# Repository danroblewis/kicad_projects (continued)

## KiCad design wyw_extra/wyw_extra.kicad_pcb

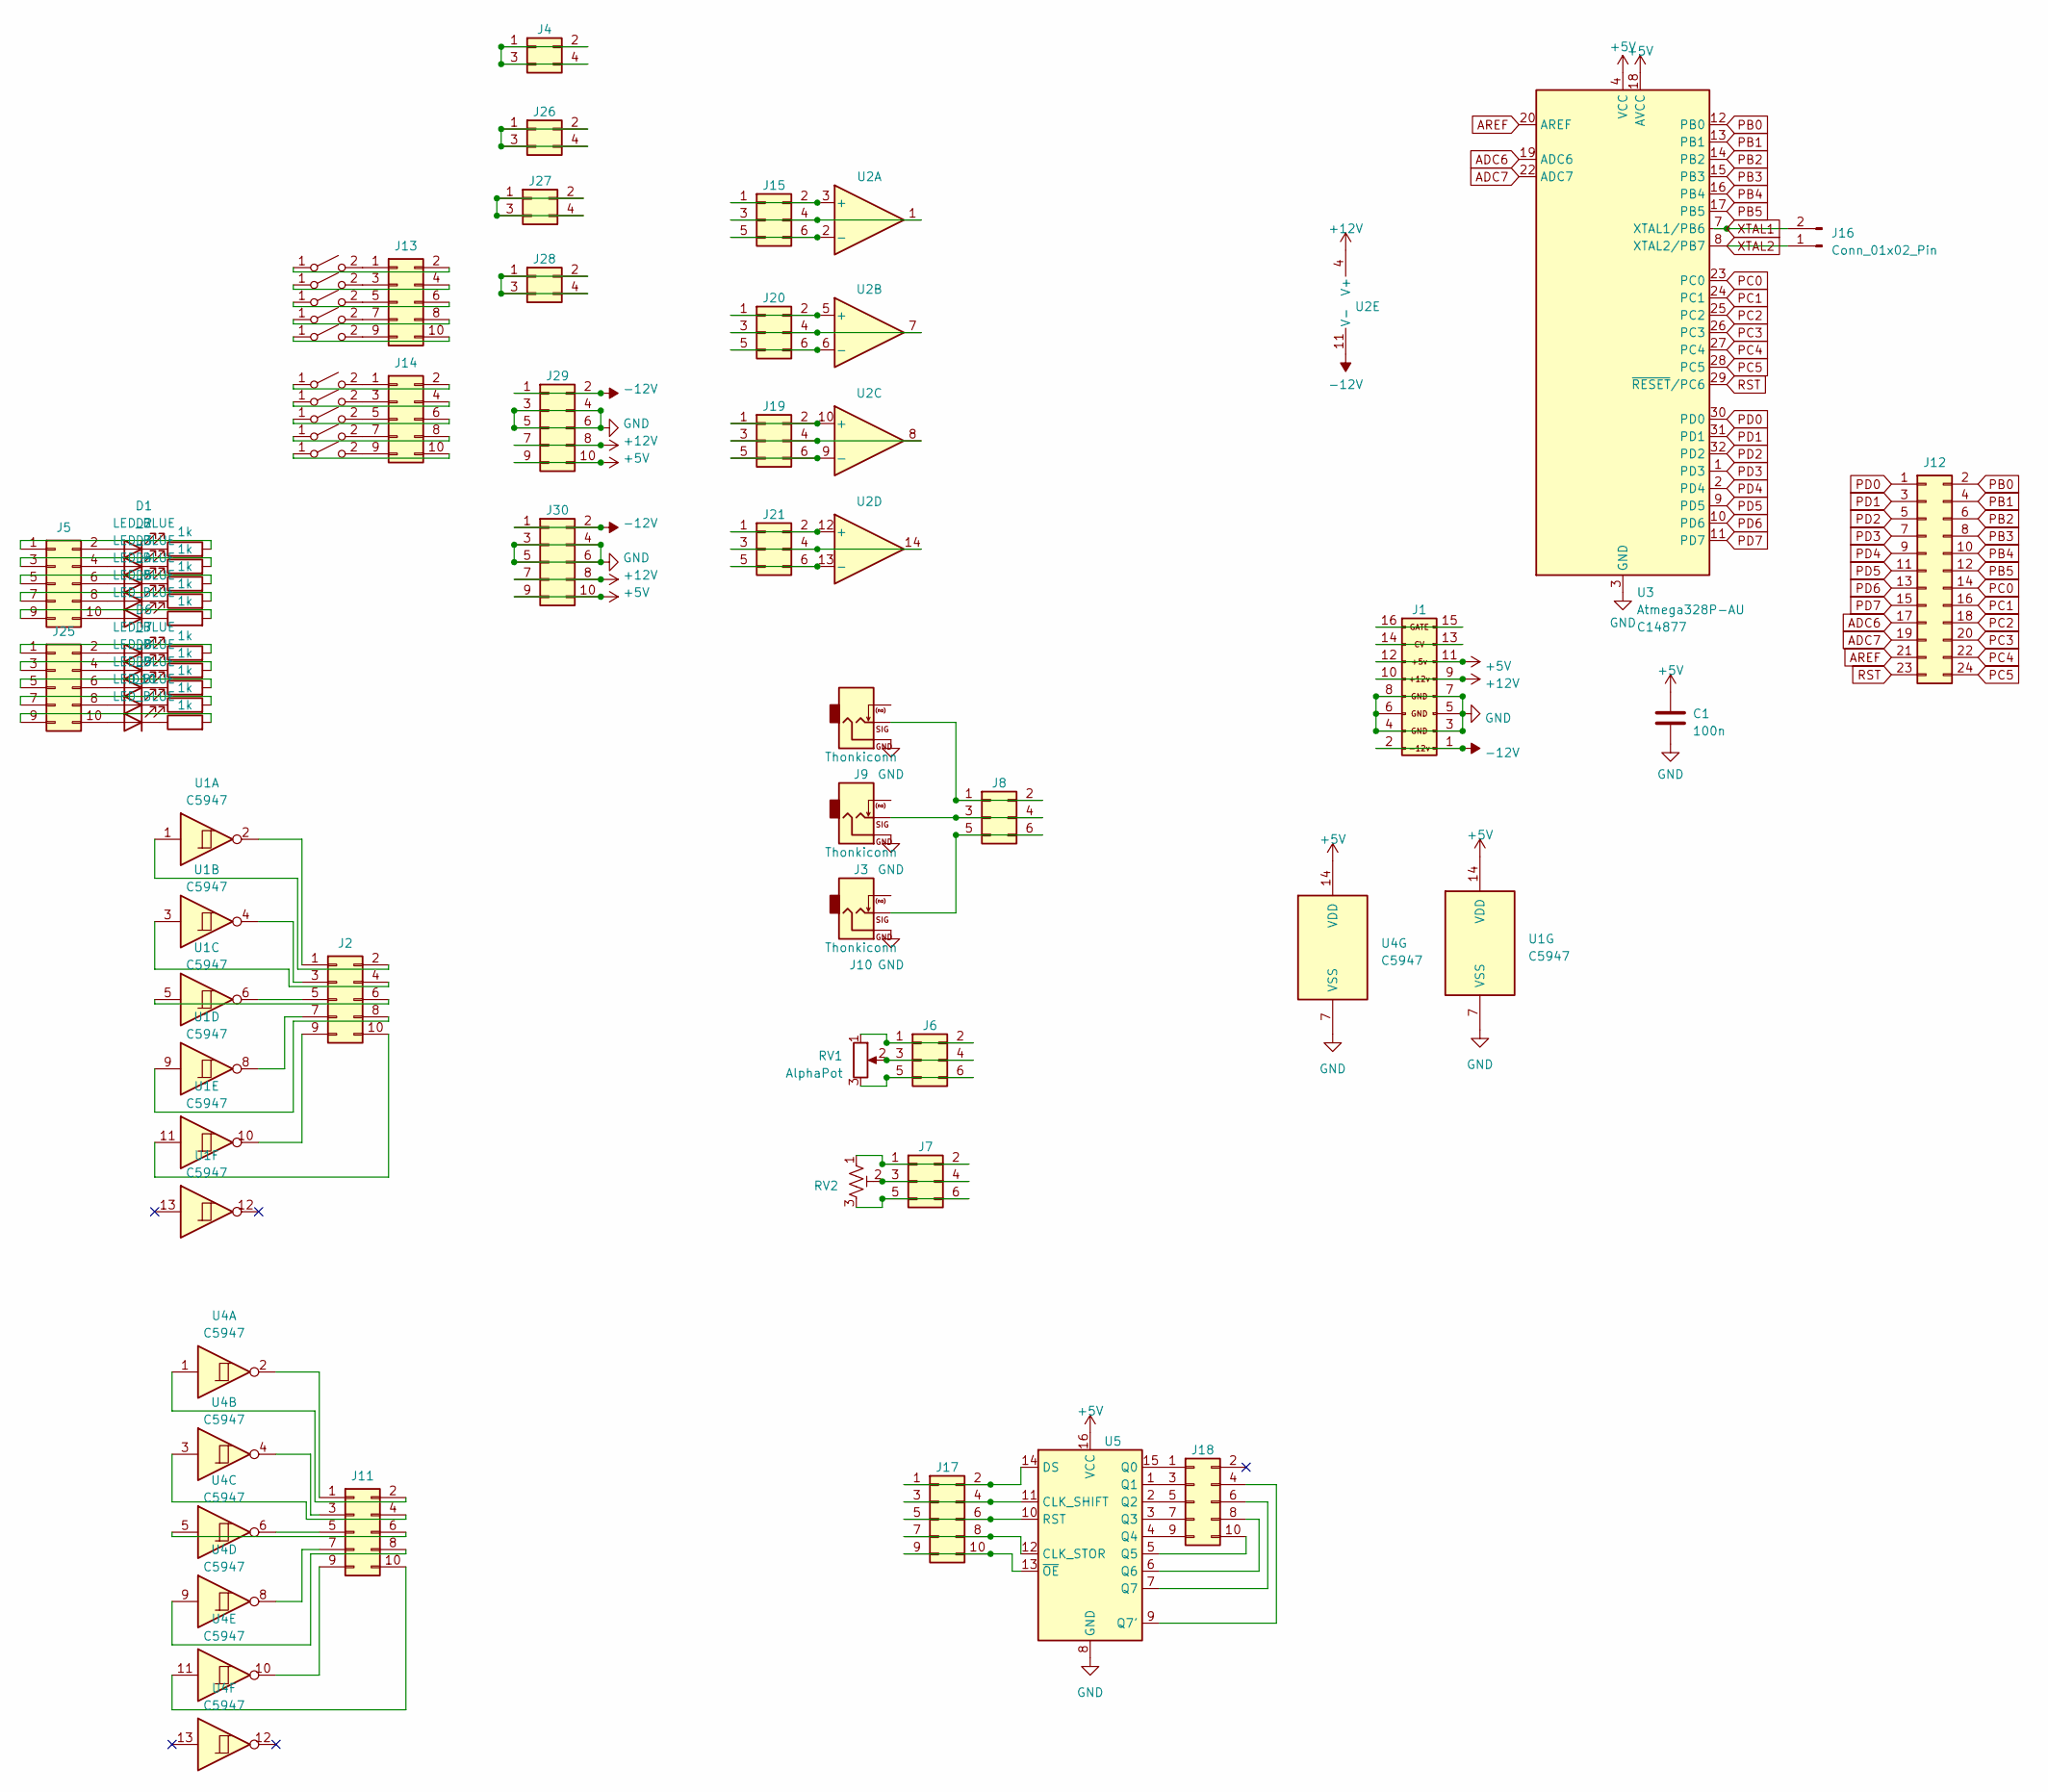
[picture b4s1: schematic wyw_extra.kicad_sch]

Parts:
C1: 100n; C_0603_1608Metric; LCSC C14663
D1, D2, D3, D4, D5, D6, D7, D8, D9, D10: LED_BLUE; LED_0603_1608Metric; LCSC C72041
J1: EuroPower16; IDC-Header_2x08_P2.54mm_Vertical; lcsc C383608
J2, J5, J11, J13, J14, J17, J18, J25, J29, J30: 02x05; PinHeader_2x05_P2.54mm_Vertical_SMD; lcsc C261072
J3, J9, J10: Thonkiconn; Jack_3.5mm_QingPu_WQP-PJ398SM_Vertical_CircularHoles
J4, J26, J27, J28: 02x02; PinHeader_2x02_P2.54mm_Vertical_SMD; lcsc C3975147
J6, J7, J8, J15, J19, J20, J21: 02x03; PinHeader_2x03_P2.54mm_Vertical_SMD; lcsc C3975148
J12: 02x12; PinHeader_2x12_P2.54mm_Vertical_SMD; lcsc C3975157
J16: Conn_01x02_Pin; PinHeader_1x02_P1.00mm_Vertical
R1, R2, R3, R4, R5, R6, R7, R8, R9, R10: 1k; R_0603_1608Metric; LCSC C21190
RV1: AlphaPot; Potentiometer_Alpha_RD901F-40-00D_Single_Vertical
RV2: R_Potentiometer_Trim_US; Potentiometer_Bourns_TC33X_Vertical; lcsc C128545
SW1, SW2, SW3, SW4, SW5, SW6, SW7, SW8, SW9, SW10: SW_SPST; SW_SPST_PTS645; lcsc C294565
U1, U4: CD40106; SOIC-16_3.9x9.9mm_P1.27mm; lcsc C5947
U2: TL074; SOIC-14_3.9x8.7mm_P1.27mm; lcsc C12594
U3: Atmega328P-AU; TQFP-32_7x7mm_P0.8mm; lcsc C14877
U5: 74HC595 8bit Shift Register; SOIC-16_3.9x9.9mm_P1.27mm; lcsc C5947

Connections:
+5V: C1.2, J1.11 (+5v_R), J1.12 (+5v_L), J29.9, J29.10, J30.9, J30.10, U1.14 (VDD), U3.4 (VCC), U3.6 (VCC), U3.18 (AVCC), U4.14 (VDD), U5.16 (VCC)
+12V: J1.9 (+12V_R), J1.10 (+12V_L), J29.7, J29.8, J30.7, J30.8, U2.4 (V+)
-12V: J1.1 (-12v_R), J1.2 (-12v_L), J29.1, J29.2, J30.1, J30.2, U2.11 (V-)
ADC6: J12.17, U3.19 (ADC6)
ADC7: J12.19, U3.22 (ADC7)
AREF: J12.21, U3.20 (AREF)
GND: C1.1, J1.3 (GND), J1.4 (GND), J1.5 (GND_R3), J1.6 (GND_L3), J1.7 (GND_R2), J1.8 (GND_L2), J3.S, J9.S, J10.S, J29.3, J29.4, J29.5, J29.6, J30.3, J30.4, J30.5, J30.6, U1.7 (VSS), U3.3 (GND), U3.5 (GND), U3.21 (GND), U4.7 (VSS), U5.8 (GND)
unnamed: D1.2 (A), J5.2
unnamed: D1.1 (K), R1.1
unnamed: D2.2 (A), J5.4
unnamed: D2.1 (K), R2.1
unnamed: D3.2 (A), J5.6
unnamed: D3.1 (K), R3.1
unnamed: D4.2 (A), J5.8
unnamed: D4.1 (K), R4.1
unnamed: D5.2 (A), J5.10
unnamed: D5.1 (K), R5.1
unnamed: D6.2 (A), J25.2
unnamed: D6.1 (K), R6.1
unnamed: D7.2 (A), J25.4
unnamed: D7.1 (K), R7.1
unnamed: D8.2 (A), J25.6
unnamed: D8.1 (K), R8.1
unnamed: D9.2 (A), J25.8
unnamed: D9.1 (K), R9.1
unnamed: D10.2 (A), J25.10
unnamed: D10.1 (K), R10.1
unnamed: J1.13 (CV_R), J1.14 (CV_L)
unnamed: J1.15 (GATE_R), J1.16 (GATE_L)
unnamed: J2.1, U1.2
unnamed: J2.2, U1.1
unnamed: J2.3, U1.4
unnamed: J2.4, U1.3
unnamed: J2.5, U1.6
unnamed: J2.6, U1.5
unnamed: J2.7, U1.8
unnamed: J2.8, U1.9
unnamed: J2.9, U1.10
unnamed: J2.10, U1.11
unnamed: J4.1, J4.2, J4.3, J4.4
unnamed: J5.1, R1.2
unnamed: J5.3, R2.2
unnamed: J5.5, R3.2
unnamed: J5.7, R4.2
unnamed: J5.9, R5.2
unnamed: J6.1, J6.2, RV1.1
unnamed: J6.3, J6.4, RV1.2
unnamed: J6.5, J6.6, RV1.3
unnamed: J7.1, J7.2, RV2.1
unnamed: J7.3, J7.4, RV2.2
unnamed: J7.5, J7.6, RV2.3
unnamed: J8.1, J8.2, J9.T
unnamed: J3.T, J8.3, J8.4
unnamed: J8.5, J8.6, J10.T
unnamed: J11.1, U4.2
unnamed: J11.2, U4.1
unnamed: J11.3, U4.4
unnamed: J11.4, U4.3
unnamed: J11.5, U4.6
unnamed: J11.6, U4.5
unnamed: J11.7, U4.8
unnamed: J11.8, U4.9
unnamed: J11.9, U4.10
unnamed: J11.10, U4.11
unnamed: J13.1, SW1.2 (B)
unnamed: J13.2, SW1.1 (A)
unnamed: J13.3, SW2.2 (B)
unnamed: J13.4, SW2.1 (A)
unnamed: J13.5, SW3.2 (B)
unnamed: J13.6, SW3.1 (A)
unnamed: J13.7, SW4.2 (B)
unnamed: J13.8, SW4.1 (A)
unnamed: J13.9, SW5.2 (B)
unnamed: J13.10, SW5.1 (A)
unnamed: J14.1, SW6.2 (B)
unnamed: J14.2, SW6.1 (A)
unnamed: J14.3, SW7.2 (B)
unnamed: J14.4, SW7.1 (A)
unnamed: J14.5, SW8.2 (B)
unnamed: J14.6, SW8.1 (A)
unnamed: J14.7, SW9.2 (B)
unnamed: J14.8, SW9.1 (A)
unnamed: J14.9, SW10.2 (B)
unnamed: J14.10, SW10.1 (A)
unnamed: J15.1, J15.2, U2.3 (+)
unnamed: J15.3, J15.4, U2.1
unnamed: J15.5, J15.6, U2.2 (-)
unnamed: J17.1, J17.2, U5.14 (DS)
unnamed: J17.3, J17.4, U5.11 (CLK_SHIFT)
unnamed: J17.5, J17.6, U5.10 (RST)
unnamed: J17.7, J17.8, U5.12 (CLK_STOR)
unnamed: J17.9, J17.10, U5.13 (~OE)
unnamed: J18.1, U5.15 (Q0)
unnamed: J18.3, U5.1 (Q1)
unnamed: J18.4, U5.9 (Q7')
unnamed: J18.5, U5.2 (Q2)
unnamed: J18.6, U5.7 (Q7)
unnamed: J18.7, U5.3 (Q3)
unnamed: J18.8, U5.6 (Q6)
unnamed: J18.9, U5.4 (Q4)
unnamed: J18.10, U5.5 (Q5)
unnamed: J19.1, J19.2, U2.10 (+)
unnamed: J19.3, J19.4, U2.8
unnamed: J19.5, J19.6, U2.9 (-)
unnamed: J20.1, J20.2, U2.5 (+)
unnamed: J20.3, J20.4, U2.7
unnamed: J20.5, J20.6, U2.6 (-)
unnamed: J21.1, J21.2, U2.12 (+)
unnamed: J21.3, J21.4, U2.14
unnamed: J21.5, J21.6, U2.13 (-)
unnamed: J25.1, R6.2
unnamed: J25.3, R7.2
unnamed: J25.5, R8.2
unnamed: J25.7, R9.2
unnamed: J25.9, R10.2
unnamed: J26.1, J26.2, J26.3, J26.4
unnamed: J27.1, J27.2, J27.3, J27.4
unnamed: J28.1, J28.2, J28.3, J28.4
PB0: J12.2, U3.12 (PB0)
PB1: J12.4, U3.13 (PB1)
PB2: J12.6, U3.14 (PB2)
PB3: J12.8, U3.15 (PB3)
PB4: J12.10, U3.16 (PB4)
PB5: J12.12, U3.17 (PB5)
PC0: J12.14, U3.23 (PC0)
PC1: J12.16, U3.24 (PC1)
PC2: J12.18, U3.25 (PC2)
PC3: J12.20, U3.26 (PC3)
PC4: J12.22, U3.27 (PC4)
PC5: J12.24, U3.28 (PC5)
PD0: J12.1, U3.30 (PD0)
PD1: J12.3, U3.31 (PD1)
PD2: J12.5, U3.32 (PD2)
PD3: J12.7, U3.1 (PD3)
PD4: J12.9, U3.2 (PD4)
PD5: J12.11, U3.9 (PD5)
PD6: J12.13, U3.10 (PD6)
PD7: J12.15, U3.11 (PD7)
RST: J12.23, U3.29 (~RESET/PC6)
XTAL1: J16.2, U3.7 (XTAL1/PB6)
XTAL2: J16.1, U3.8 (XTAL2/PB7)

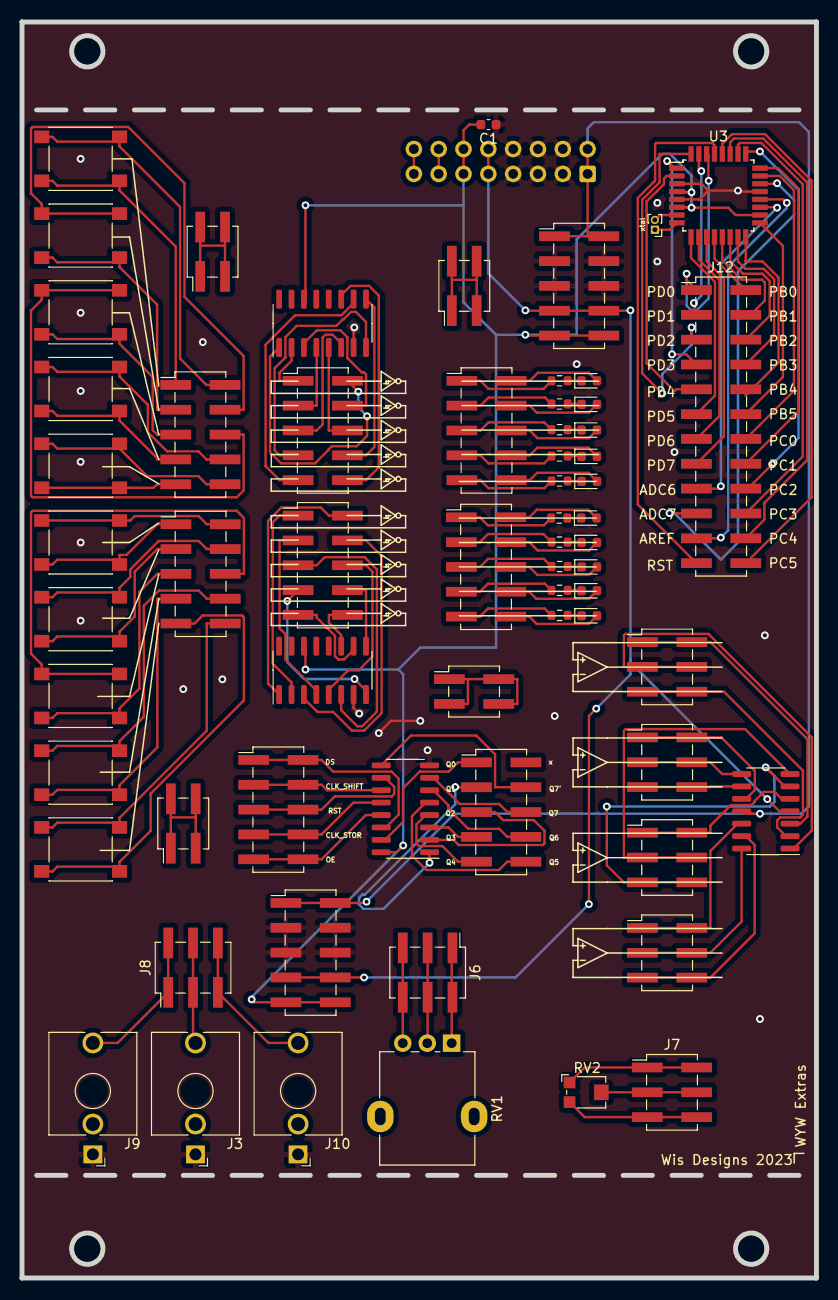
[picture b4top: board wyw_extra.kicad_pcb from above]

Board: 2 copper layers, 81.3 x 128.5 mm, 65 parts (1 on the bottom side), 141 nets.

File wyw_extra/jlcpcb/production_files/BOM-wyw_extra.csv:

Comment,Designator,Footprint,LCSC
TL074,U2,SOIC-14_3.9x8.7mm_P1.27mm,C12594
R_Potentiometer_Trim_US,RV2,Potentiometer_Bourns_TC33X_Vertical,C128545
100n,C1,C_0603_1608Metric,C14663
Atmega328P-AU,U3,TQFP-32_7x7mm_P0.8mm,C14877
1k,"R1,R10,R2,R3,R4,R5,R6,R7,R8,R9",R_0603_1608Metric,C21190
02x05,"J11,J13,J14,J17,J18,J2,J25,J29,J30,J5",PinHeader_2x05_P2.54mm_Vertical_SMD,C261072
SW_SPST,"SW1,SW10,SW2,SW3,SW4,SW5,SW6,SW7,SW8,SW9",SW_SPST_PTS645,C294565
EuroPower16,J1,IDC-Header_2x08_P2.54mm_Vertical,C383608
02x02,"J26,J27,J28,J4",PinHeader_2x02_P2.54mm_Vertical_SMD,C3975147
02x03,"J15,J19,J20,J21,J6,J7,J8",PinHeader_2x03_P2.54mm_Vertical_SMD,C3975148
02x12,J12,PinHeader_2x12_P2.54mm_Vertical_SMD,C3975157
CD40106,"U1,U4,U5",SOIC-16_3.9x9.9mm_P1.27mm,C5947
LED_BLUE,"D1,D10,D2,D3,D4,D5,D6,D7,D8,D9",LED_0603_1608Metric,C72041
AlphaPot,RV1,Potentiometer_Alpha_RD901F-40-00D_Single_Vertical,
Conn_01x02_Pin,J16,PinHeader_1x02_P1.00mm_Vertical,

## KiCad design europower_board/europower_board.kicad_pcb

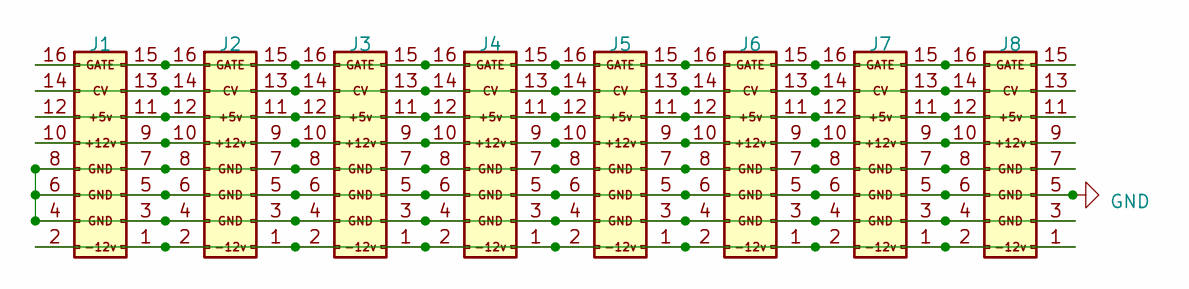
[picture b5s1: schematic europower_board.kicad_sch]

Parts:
J1, J2, J3, J4, J5, J6, J7, J8: EuroPower16; IDC-Header_2x08_P2.54mm_Vertical_SMD; lcsc C383608

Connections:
GND: J1.3 (GND), J1.4 (GND), J1.5 (GND_R3), J1.6 (GND_L3), J1.7 (GND_R2), J1.8 (GND_L2), J2.3 (GND), J2.4 (GND), J2.5 (GND_R3), J2.6 (GND_L3), J2.7 (GND_R2), J2.8 (GND_L2), J3.3 (GND), J3.4 (GND), J3.5 (GND_R3), J3.6 (GND_L3), J3.7 (GND_R2), J3.8 (GND_L2), J4.3 (GND), J4.4 (GND), J4.5 (GND_R3), J4.6 (GND_L3), J4.7 (GND_R2), J4.8 (GND_L2), J5.3 (GND), J5.4 (GND), J5.5 (GND_R3), J5.6 (GND_L3), J5.7 (GND_R2), J5.8 (GND_L2), J6.3 (GND), J6.4 (GND), J6.5 (GND_R3), J6.6 (GND_L3), J6.7 (GND_R2), J6.8 (GND_L2), J7.3 (GND), J7.4 (GND), J7.5 (GND_R3), J7.6 (GND_L3), J7.7 (GND_R2), J7.8 (GND_L2), J8.3 (GND), J8.4 (GND), J8.5 (GND_R3), J8.6 (GND_L3), J8.7 (GND_R2), J8.8 (GND_L2)
unnamed: J1.11 (+5v_R), J1.12 (+5v_L), J2.11 (+5v_R), J2.12 (+5v_L), J3.11 (+5v_R), J3.12 (+5v_L), J4.11 (+5v_R), J4.12 (+5v_L), J5.11 (+5v_R), J5.12 (+5v_L), J6.11 (+5v_R), J6.12 (+5v_L), J7.11 (+5v_R), J7.12 (+5v_L), J8.11 (+5v_R), J8.12 (+5v_L)
unnamed: J1.9 (+12V_R), J1.10 (+12V_L), J2.9 (+12V_R), J2.10 (+12V_L), J3.9 (+12V_R), J3.10 (+12V_L), J4.9 (+12V_R), J4.10 (+12V_L), J5.9 (+12V_R), J5.10 (+12V_L), J6.9 (+12V_R), J6.10 (+12V_L), J7.9 (+12V_R), J7.10 (+12V_L), J8.9 (+12V_R), J8.10 (+12V_L)
unnamed: J1.1 (-12v_R), J1.2 (-12v_L), J2.1 (-12v_R), J2.2 (-12v_L), J3.1 (-12v_R), J3.2 (-12v_L), J4.1 (-12v_R), J4.2 (-12v_L), J5.1 (-12v_R), J5.2 (-12v_L), J6.1 (-12v_R), J6.2 (-12v_L), J7.1 (-12v_R), J7.2 (-12v_L), J8.1 (-12v_R), J8.2 (-12v_L)
unnamed: J1.13 (CV_R), J1.14 (CV_L), J2.13 (CV_R), J2.14 (CV_L), J3.13 (CV_R), J3.14 (CV_L), J4.13 (CV_R), J4.14 (CV_L), J5.13 (CV_R), J5.14 (CV_L), J6.13 (CV_R), J6.14 (CV_L), J7.13 (CV_R), J7.14 (CV_L), J8.13 (CV_R), J8.14 (CV_L)
unnamed: J1.15 (GATE_R), J1.16 (GATE_L), J2.15 (GATE_R), J2.16 (GATE_L), J3.15 (GATE_R), J3.16 (GATE_L), J4.15 (GATE_R), J4.16 (GATE_L), J5.15 (GATE_R), J5.16 (GATE_L), J6.15 (GATE_R), J6.16 (GATE_L), J7.15 (GATE_R), J7.16 (GATE_L), J8.15 (GATE_R), J8.16 (GATE_L)

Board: 2 copper layers, 8 parts (0 on the bottom side), 6 nets, no tracks yet.

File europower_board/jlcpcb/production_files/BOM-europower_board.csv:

Comment,Designator,Footprint,LCSC
EuroPower16,"J1,J2,J3,J4,J5,J6,J7,J8",IDC-Header_2x08_P2.54mm_Vertical_SMD,C383608

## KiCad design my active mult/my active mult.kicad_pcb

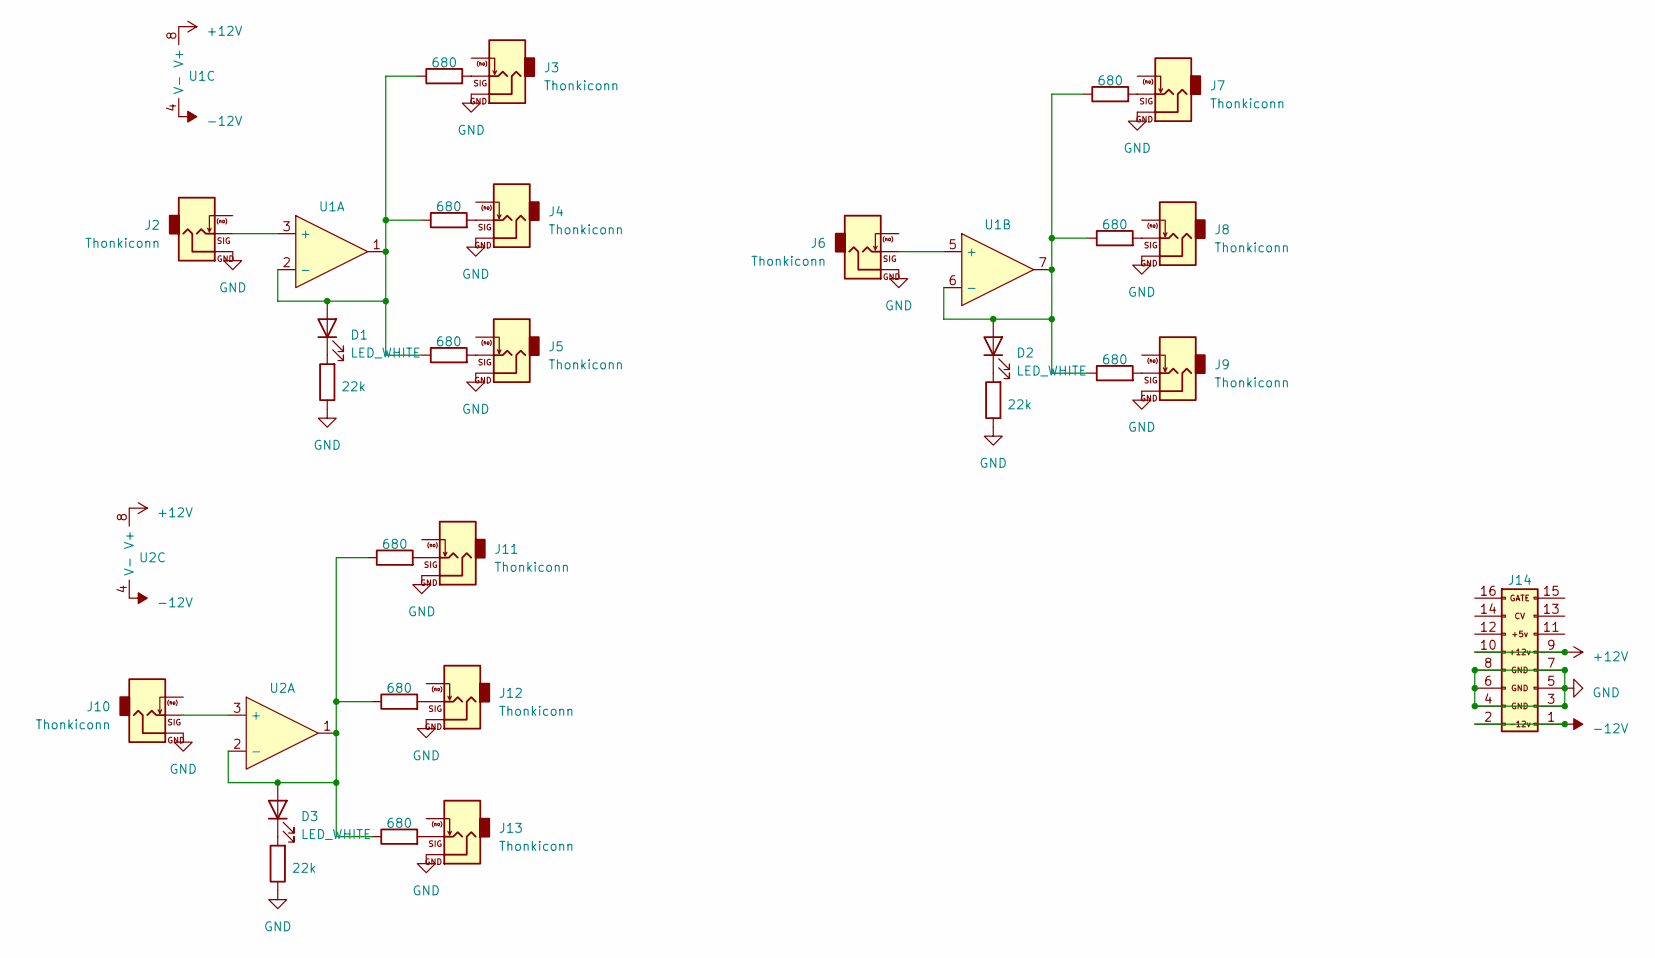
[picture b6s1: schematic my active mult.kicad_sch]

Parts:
D1, D2, D3: LED_WHITE; LED_0603_1608Metric; LCSC C2290
J2, J3, J4, J5, J6, J7, J8, J9, J10, J11, J12, J13: Thonkiconn; Jack_3.5mm_QingPu_WQP-PJ398SM_Vertical_CircularHoles
J14: EuroPower16; IDC-Header_2x08_P2.54mm_Vertical_SMD; lcsc C383608
R1, R5, R9: 22k; R_0603_1608Metric; LCSC C31850
R2, R3, R4, R6, R7, R8, R10, R11, R12: 680; R_0603_1608Metric; LCSC C23228
U1, U2: TL072; SOIC-8_3.9x4.9mm_P1.27mm; LCSC C6961

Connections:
+12V: J14.9 (+12V_R), J14.10 (+12V_L), U1.8 (V+), U2.8 (V+)
-12V: J14.1 (-12v_R), J14.2 (-12v_L), U1.4 (V-), U2.4 (V-)
GND: J2.S, J3.S, J4.S, J5.S, J6.S, J7.S, J8.S, J9.S, J10.S, J11.S, J12.S, J13.S, J14.3 (GND), J14.4 (GND), J14.5 (GND_R3), J14.6 (GND_L3), J14.7 (GND_R2), J14.8 (GND_L2), R1.1, R5.1, R9.1
unnamed: D1.2 (A), R2.1, R3.1, R4.1, U1.1, U1.2 (-)
unnamed: D1.1 (K), R1.2
unnamed: D2.2 (A), R6.1, R7.1, R8.1, U1.6 (-), U1.7
unnamed: D2.1 (K), R5.2
unnamed: D3.2 (A), R10.1, R11.1, R12.1, U2.1, U2.2 (-)
unnamed: D3.1 (K), R9.2
unnamed: J3.T, R2.2
unnamed: J4.T, R3.2
unnamed: J5.T, R4.2
unnamed: J7.T, R6.2
unnamed: J8.T, R7.2
unnamed: J9.T, R8.2
unnamed: J11.T, R10.2
unnamed: J12.T, R11.2
unnamed: J13.T, R12.2
unnamed: J2.T, U1.3 (+)
unnamed: J6.T, U1.5 (+)
unnamed: J10.T, U2.3 (+)

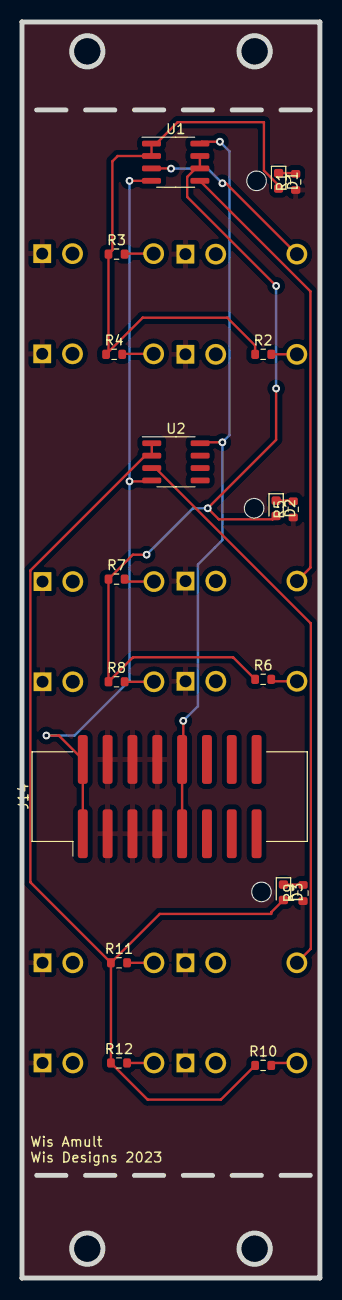
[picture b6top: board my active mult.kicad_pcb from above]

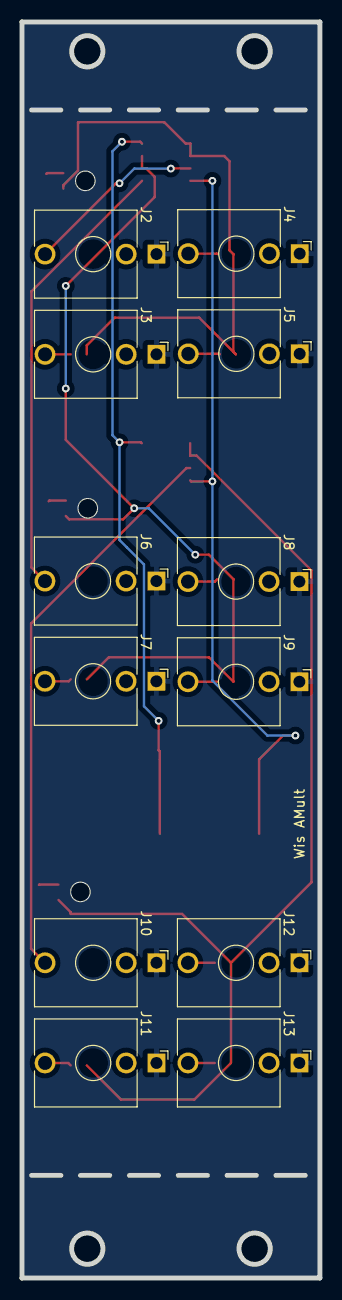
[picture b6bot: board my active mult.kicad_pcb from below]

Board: 2 copper layers, 30.5 x 128.5 mm, 30 parts (12 on the bottom side), 21 nets.

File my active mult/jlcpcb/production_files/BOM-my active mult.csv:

Comment,Designator,Footprint,LCSC
LED_WHITE,"D1,D2,D3",LED_0603_1608Metric,C2290
680,"R10,R11,R12,R2,R3,R4,R6,R7,R8",R_0603_1608Metric,C23228
22k,"R1,R5,R9",R_0603_1608Metric,C31850
EuroPower16,J14,IDC-Header_2x08_P2.54mm_Vertical_SMD,C383608
TL072,"U1,U2",SOIC-8_3.9x4.9mm_P1.27mm,C6961

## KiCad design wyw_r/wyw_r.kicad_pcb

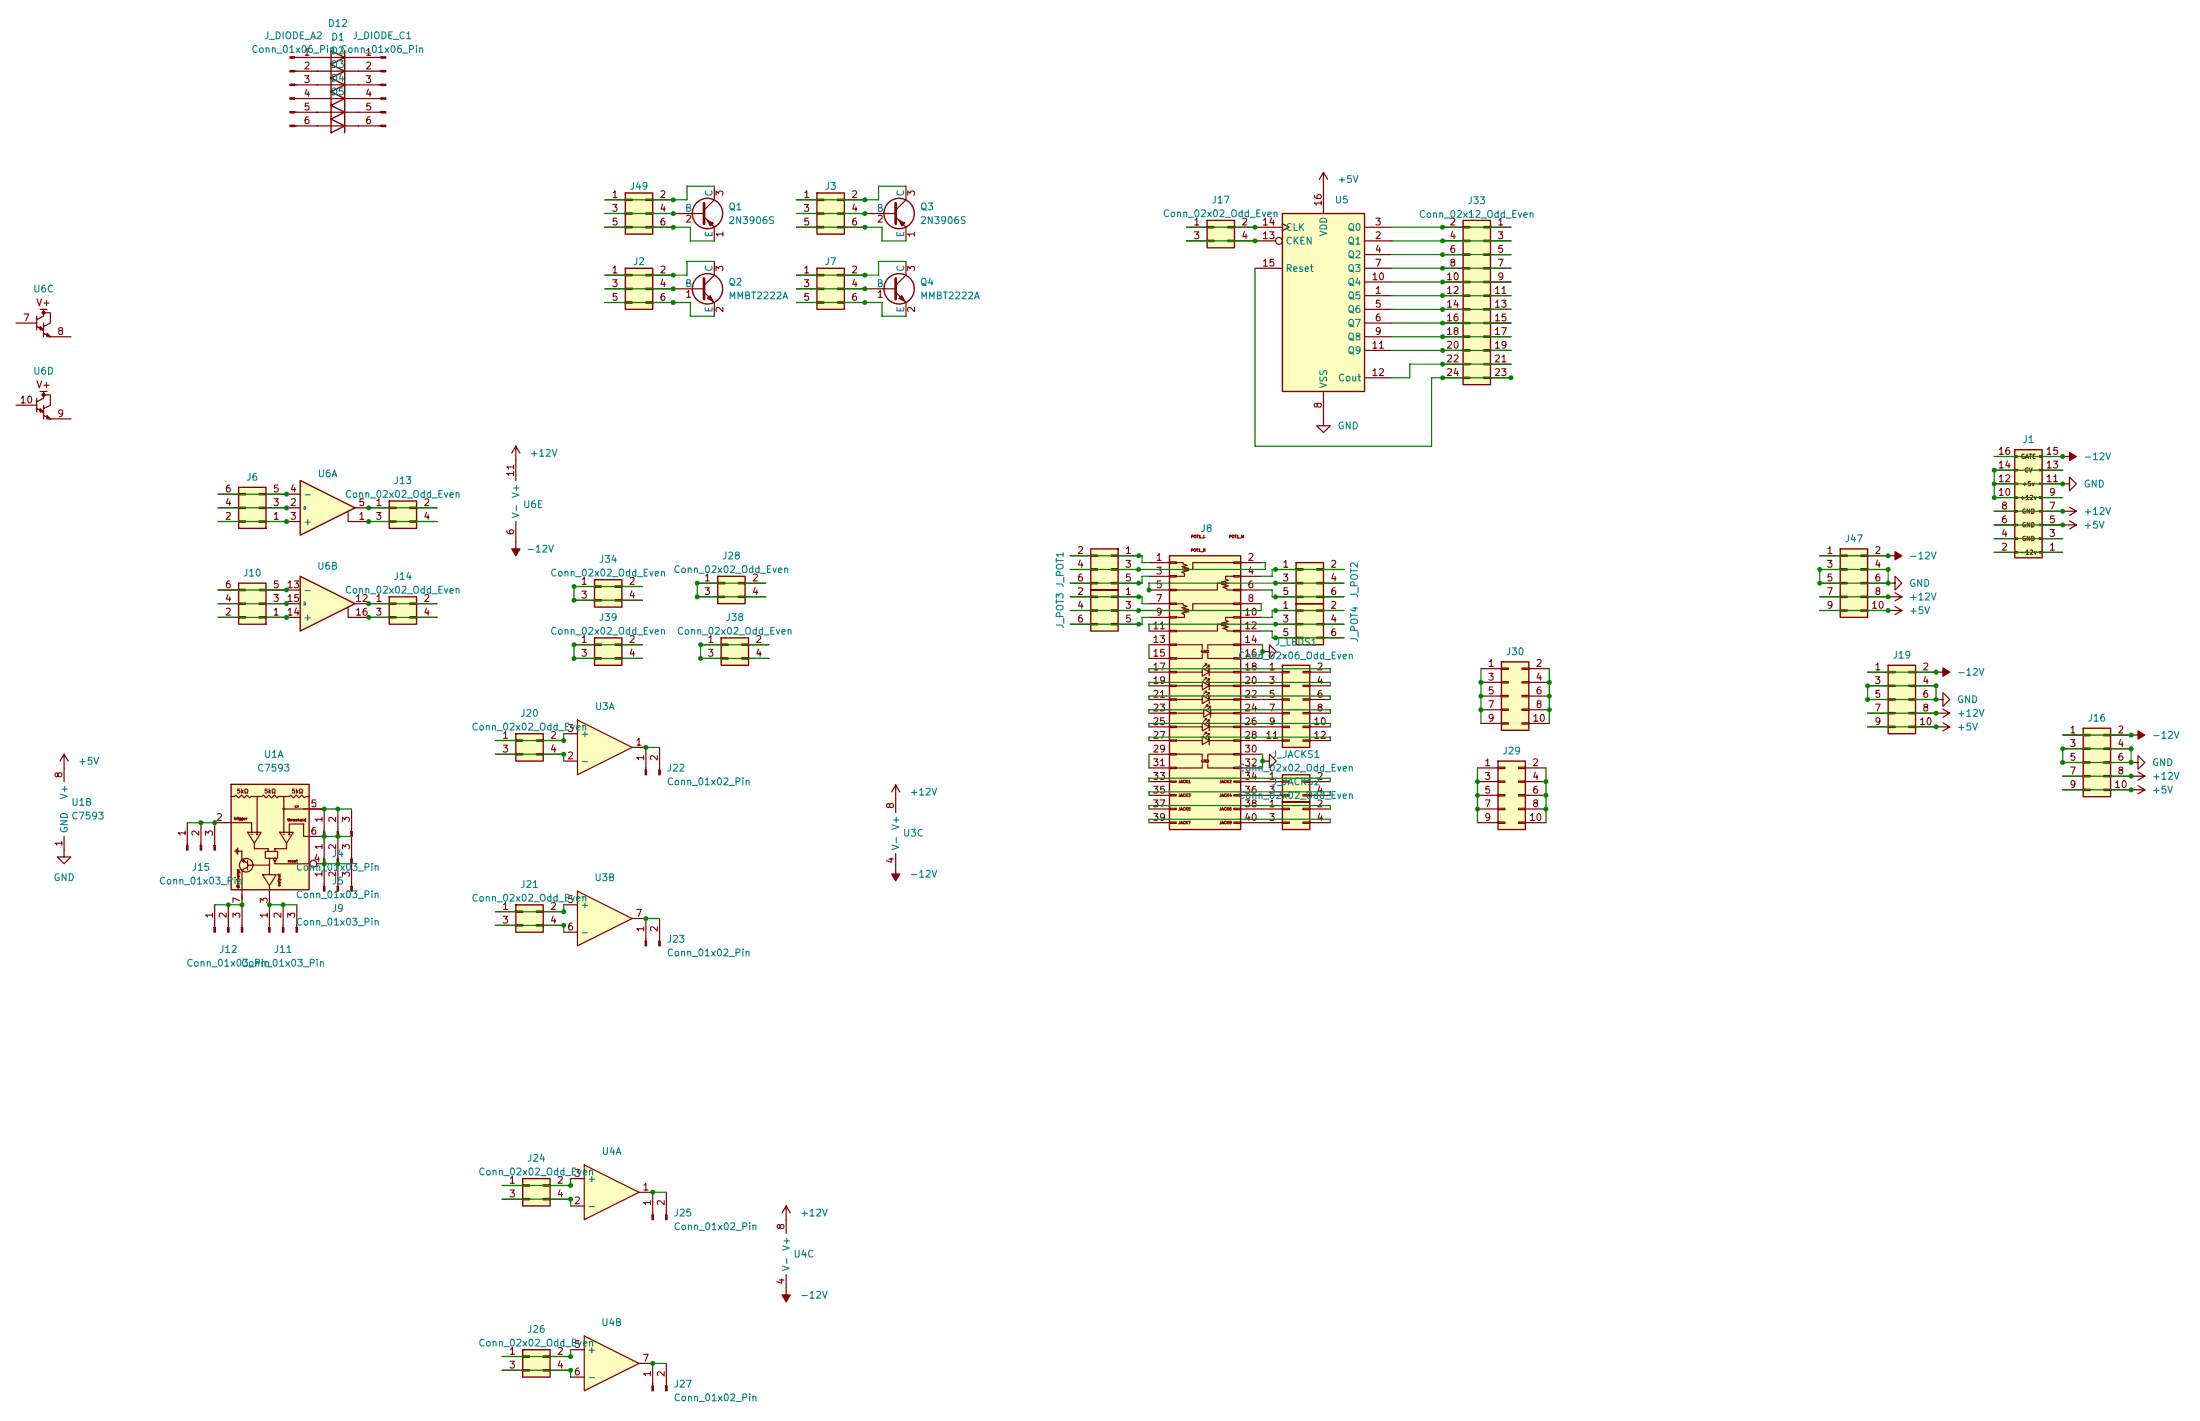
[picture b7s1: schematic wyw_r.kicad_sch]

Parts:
D1, D2, D3, D4, D5, D12: 1N4148WS; D_SOD-323; LCSC C2128
J1: EuroPower16; IDC-Header_2x08_P2.54mm_Vertical_SMD; lcsc C383608
J2, J3, J6, J7, J10, J49: 02x03; PinHeader_2x03_P2.54mm_Vertical
J4, J5, J9, J11, J12, J15: Conn_01x03_Pin; PinHeader_1x03_P2.54mm_Vertical
J8: male 02x20; PinHeader_2x20_P2.54mm_Horizontal; lcsc C5149370
J13, J14, J17, J20, J21, J24, J26, J28, J34, J38, J39: Conn_02x02_Odd_Even; PinHeader_2x02_P2.54mm_Vertical
J16, J19, J29, J30, J47: 02x05; PinHeader_2x05_P2.54mm_Vertical
J22, J23, J25, J27: Conn_01x02_Pin; PinHeader_1x02_P2.54mm_Vertical
J33: Conn_02x12_Odd_Even; PinHeader_2x12_P2.54mm_Vertical
J_DIODE_A2: Conn_01x06_Pin; PinHeader_1x06_P2.54mm_Vertical
J_DIODE_C1: Conn_01x06_Pin; PinHeader_1x06_P2.54mm_Vertical
J_JACKS1, J_JACKS2: Conn_02x02_Odd_Even; PinHeader_2x02_P2.54mm_Vertical
J_LEDS1: Conn_02x06_Odd_Even; PinHeader_2x06_P2.54mm_Vertical
J_POT1, J_POT2, J_POT3, J_POT4: 02x03; PinHeader_2x03_P2.54mm_Vertical
Q1, Q3: 2N3906S; SOT-23-3; LCSC C147294
Q2, Q4: MMBT2222A; SOT-23-3; LCSC C8512
U1: NE555DR; SOIC-8-1EP_3.9x4.9mm_P1.27mm_EP2.29x3mm; LCSC C7593
U3, U4: TL072; SOIC-8_3.9x4.9mm_P1.27mm; LCSC C6961
U5: 4017bm; SOP-16_3.9x9.9mm_P1.27mm; LCSC C356694
U6: XL13700; SOP-16_3.9x9.9mm_P1.27mm; LCSC C521166

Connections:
+5V: J1.5 (GND_R3), J1.6 (GND_L3), J16.9, J16.10, J19.9, J19.10, J47.9, J47.10, U1.8 (V+), U5.16 (VDD)
+12V: J1.7 (GND_R2), J1.8 (GND_L2), J16.7, J16.8, J19.7, J19.8, J47.7, J47.8, U3.8 (V+), U4.8 (V+), U6.11 (V+)
-12V: J1.15 (GATE_R), J1.16 (GATE_L), J16.1, J16.2, J19.1, J19.2, J47.1, J47.2, U3.4 (V-), U4.4 (V-), U6.6 (V-)
GND: J1.9 (+12V_R), J1.10 (+12V_L), J1.11 (+5v_R), J1.12 (+5v_L), J1.13 (CV_R), J1.14 (CV_L), J8.14, J8.16, J8.30, J8.32, J16.3, J16.4, J16.5, J16.6, J19.3, J19.4, J19.5, J19.6, J47.3, J47.4, J47.5, J47.6, U1.1 (GND), U5.8 (VSS)
unnamed: D1.2 (A), J_DIODE_A2.2
unnamed: D1.1 (K), J_DIODE_C1.2
unnamed: D2.2 (A), J_DIODE_A2.3
unnamed: D2.1 (K), J_DIODE_C1.3
unnamed: D3.2 (A), J_DIODE_A2.4
unnamed: D3.1 (K), J_DIODE_C1.4
unnamed: D4.2 (A), J_DIODE_A2.5
unnamed: D4.1 (K), J_DIODE_C1.5
unnamed: D5.2 (A), J_DIODE_A2.6
unnamed: D5.1 (K), J_DIODE_C1.6
unnamed: D12.2 (A), J_DIODE_A2.1
unnamed: D12.1 (K), J_DIODE_C1.1
unnamed: J1.1 (-12v_R), J1.2 (-12v_L)
unnamed: J1.3 (GND), J1.4 (GND)
unnamed: J2.1, J2.2, Q2.3 (C)
unnamed: J2.3, J2.4, Q2.1 (B)
unnamed: J2.5, J2.6, Q2.2 (E)
unnamed: J3.1, J3.2, Q3.3 (C)
unnamed: J3.3, J3.4, Q3.2 (B)
unnamed: J3.5, J3.6, Q3.1 (E)
unnamed: J4.1, J4.2, J4.3, U1.5
unnamed: J5.1, J5.2, J5.3, U1.6
unnamed: J6.1, J6.2, U6.3 (+)
unnamed: J6.3, J6.4, U6.2 (D)
unnamed: J6.5, J6.6, U6.4 (-)
unnamed: J7.1, J7.2, Q4.3 (C)
unnamed: J7.3, J7.4, Q4.1 (B)
unnamed: J7.5, J7.6, Q4.2 (E)
unnamed: J8.1, J_POT1.1, J_POT1.2
unnamed: J8.2, J_POT1.3, J_POT1.4
unnamed: J8.3, J_POT1.5, J_POT1.6
unnamed: J8.4, J_POT2.1, J_POT2.2
unnamed: J8.5, J_POT2.3, J_POT2.4
unnamed: J8.6, J_POT2.5, J_POT2.6
unnamed: J8.7, J_POT3.1, J_POT3.2
unnamed: J8.8, J_POT3.3, J_POT3.4
unnamed: J8.9, J_POT3.5, J_POT3.6
unnamed: J8.10, J_POT4.1, J_POT4.2
unnamed: J8.11, J_POT4.3, J_POT4.4
unnamed: J8.12, J_POT4.5, J_POT4.6
unnamed: J8.13, J8.15
unnamed: J8.17, J_LEDS1.2
unnamed: J8.18, J_LEDS1.1
unnamed: J8.19, J_LEDS1.4
unnamed: J8.20, J_LEDS1.3
unnamed: J8.21, J_LEDS1.6
unnamed: J8.22, J_LEDS1.5
unnamed: J8.23, J_LEDS1.8
unnamed: J8.24, J_LEDS1.7
unnamed: J8.25, J_LEDS1.10
unnamed: J8.26, J_LEDS1.9
unnamed: J8.27, J_LEDS1.12
unnamed: J8.28, J_LEDS1.11
unnamed: J8.29, J8.31
unnamed: J8.33, J_JACKS1.2
unnamed: J8.34, J_JACKS1.1
unnamed: J8.35, J_JACKS1.4
unnamed: J8.36, J_JACKS1.3
unnamed: J8.37, J_JACKS2.2
unnamed: J8.38, J_JACKS2.1
unnamed: J8.39, J_JACKS2.4
unnamed: J8.40, J_JACKS2.3
unnamed: J9.1, J9.2, J9.3, U1.4
unnamed: J10.1, J10.2, U6.14 (+)
unnamed: J10.3, J10.4, U6.15 (D)
unnamed: J10.5, J10.6, U6.13 (-)
unnamed: J11.1, J11.2, J11.3, U1.3
unnamed: J12.1, J12.2, J12.3, U1.7
unnamed: J13.1, J13.2, U6.5
unnamed: J13.3, J13.4, U6.1
unnamed: J14.1, J14.2, U6.12
unnamed: J14.3, J14.4, U6.16
unnamed: J15.1, J15.2, J15.3, U1.2
unnamed: J17.1, J17.2, U5.14 (CLK)
unnamed: J17.3, J17.4, U5.13 (CKEN)
unnamed: J20.1, J20.2, U3.3 (+)
unnamed: J20.3, J20.4, U3.2 (-)
unnamed: J21.1, J21.2, U3.5 (+)
unnamed: J21.3, J21.4, U3.6 (-)
unnamed: J22.1, J22.2, U3.1
unnamed: J23.1, J23.2, U3.7
unnamed: J24.1, J24.2, U4.3 (+)
unnamed: J24.3, J24.4, U4.2 (-)
unnamed: J25.1, J25.2, U4.1
unnamed: J26.1, J26.2, U4.5 (+)
unnamed: J26.3, J26.4, U4.6 (-)
unnamed: J27.1, J27.2, U4.7
unnamed: J28.1, J28.2, J28.3, J28.4
unnamed: J29.1, J29.3, J29.5, J29.7, J29.9
unnamed: J29.2, J29.4, J29.6, J29.8, J29.10
unnamed: J30.1, J30.3, J30.5, J30.7, J30.9
unnamed: J30.2, J30.4, J30.6, J30.8, J30.10
unnamed: J33.1, J33.2, U5.3 (Q0)
unnamed: J33.3, J33.4, U5.2 (Q1)
unnamed: J33.5, J33.6, U5.4 (Q2)
unnamed: J33.7, J33.8, U5.7 (Q3)
unnamed: J33.9, J33.10, U5.10 (Q4)
unnamed: J33.11, J33.12, U5.1 (Q5)
unnamed: J33.13, J33.14, U5.5 (Q6)
unnamed: J33.15, J33.16, U5.6 (Q7)
unnamed: J33.17, J33.18, U5.9 (Q8)
unnamed: J33.19, J33.20, U5.11 (Q9)
unnamed: J33.21, J33.22, U5.12 (Cout)
unnamed: J33.23, J33.24, U5.15 (Reset)
unnamed: J34.1, J34.2, J34.3, J34.4
unnamed: J38.1, J38.2, J38.3, J38.4
unnamed: J39.1, J39.2, J39.3, J39.4
unnamed: J49.1, J49.2, Q1.3 (C)
unnamed: J49.3, J49.4, Q1.2 (B)
unnamed: J49.5, J49.6, Q1.1 (E)

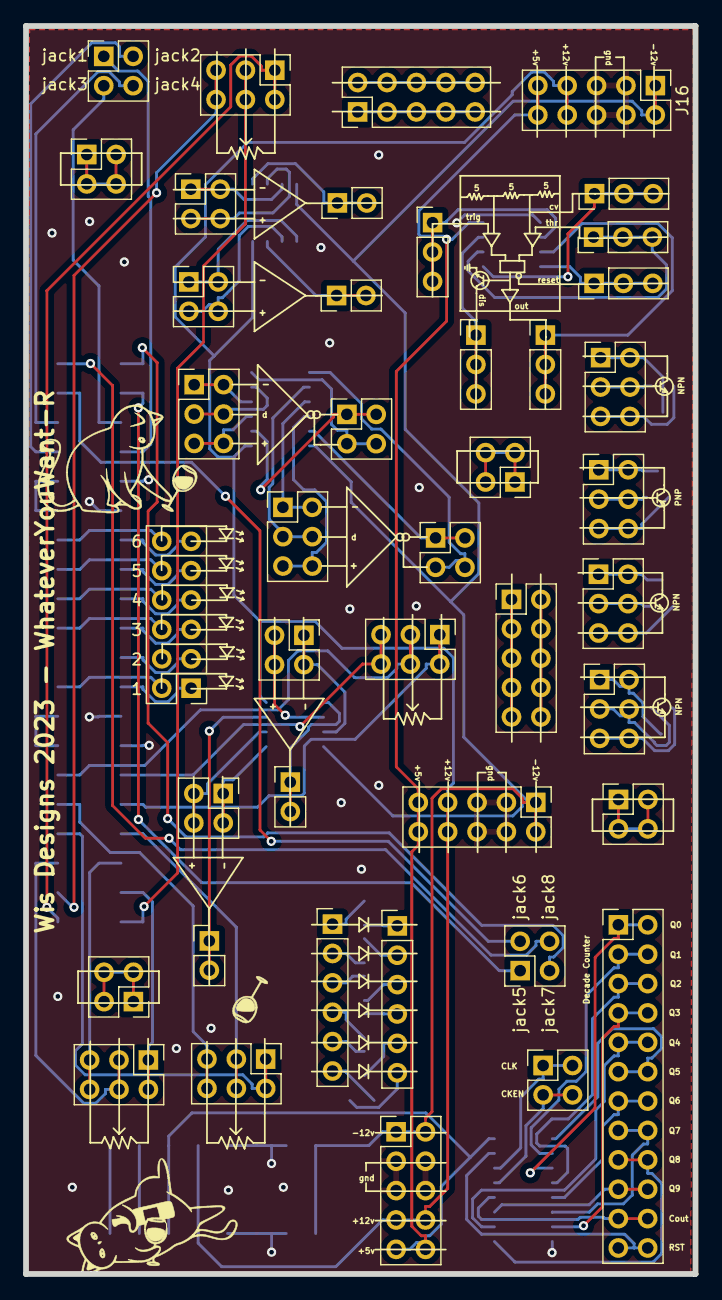
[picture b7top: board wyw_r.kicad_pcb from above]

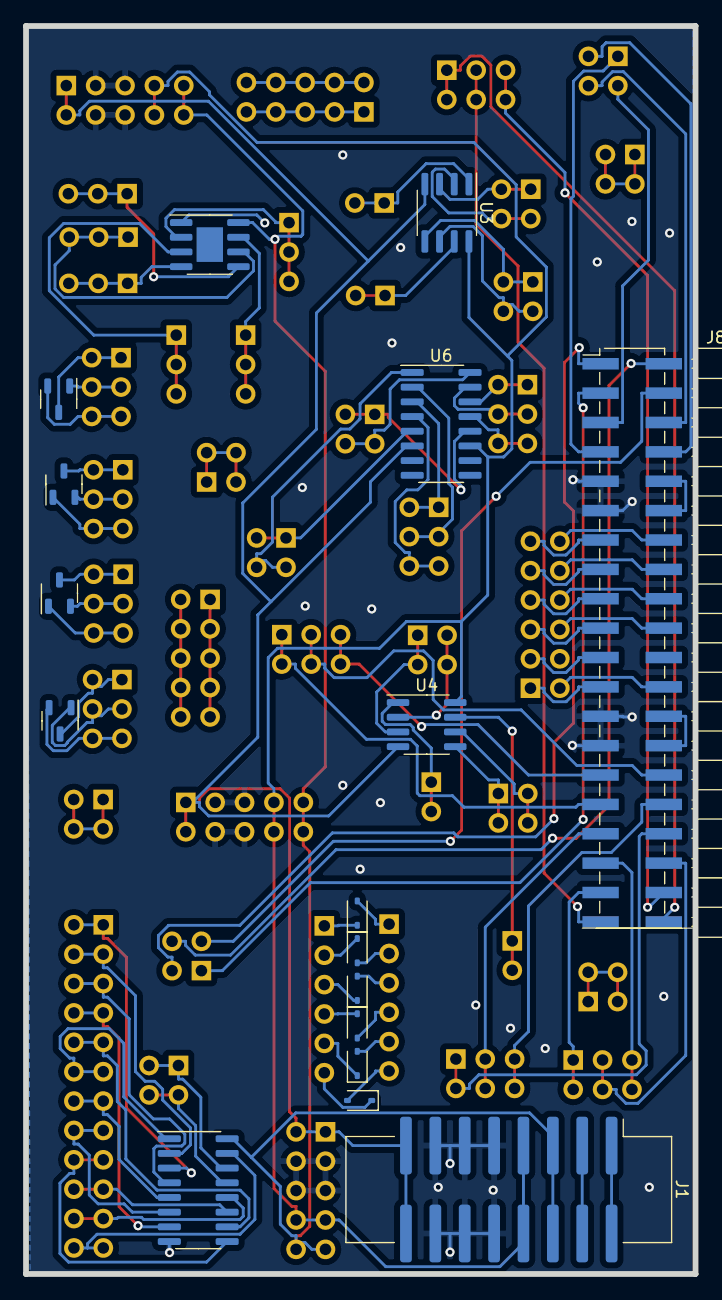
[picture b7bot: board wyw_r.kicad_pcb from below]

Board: 2 copper layers, 57.9 x 107.9 mm, 59 parts (17 on the bottom side), 114 nets.

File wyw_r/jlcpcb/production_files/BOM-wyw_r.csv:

Comment,Designator,Footprint,LCSC
2N3906S,"Q1,Q3",SOT-23-3,C147294
1N4148WS,"D1,D12,D2,D3,D4,D5",D_SOD-323,C2128
4017bm,U5,SOP-16_3.9x9.9mm_P1.27mm,C356694
EuroPower16,J1,IDC-Header_2x08_P2.54mm_Vertical_SMD,C383608
male 02x20,J8,PinHeader_2x20_P2.54mm_Horizontal,C5149370
XL13700,U6,SOP-16_3.9x9.9mm_P1.27mm,C521166
TL072,"U3,U4",SOIC-8_3.9x4.9mm_P1.27mm,C6961
NE555DR,U1,SOIC-8-1EP_3.9x4.9mm_P1.27mm_EP2.29x3mm,C7593
MMBT2222A,"Q2,Q4",SOT-23-3,C8512
